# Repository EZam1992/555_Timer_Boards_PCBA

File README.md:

# 555 Timer Board

## Overview

The 555 Timer Board is a beginner-friendly electronics project designed to introduce the author to the process of designing and manufacturing printed circuit boards (PCBs). Using the versatile 555 timer IC, this board provides practical experience with electronic circuit design and real-world prototyping.

---

*Created by Erick Stanley Zamora*  
[erickstanleyzamora.com](https://www.erickstanleyzamora.com/projects/555-timer-board)

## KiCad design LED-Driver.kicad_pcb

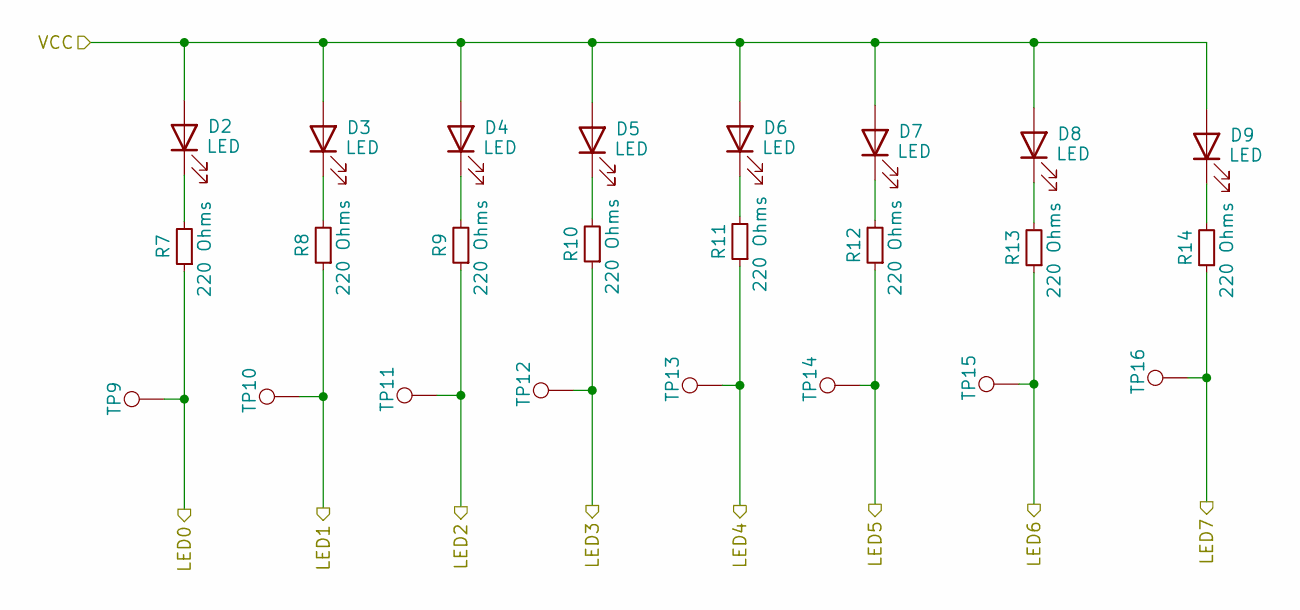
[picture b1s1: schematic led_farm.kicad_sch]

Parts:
D2, D3, D4, D5, D6, D7, D8, D9: LED; LED_D5.0mm
R7, R8, R9, R10, R11, R12, R13, R14: 220 Ohms; R_Axial_DIN0309_L9.0mm_D3.2mm_P12.70mm_Horizontal
TP9, TP10, TP11, TP12, TP13, TP14, TP15, TP16: TestPoint; TestPoint_Loop_D2.50mm_Drill1.0mm_LowProfile

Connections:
/Clock Generation/VCC: D2.2 (A), D3.2 (A), D4.2 (A), D5.2 (A), D6.2 (A), D7.2 (A), D8.2 (A), D9.2 (A); also elsewhere on the board
/Decoder/LED0: R7.1, TP9.1; also elsewhere on the board
/Decoder/LED1: R8.1, TP10.1; also elsewhere on the board
/Decoder/LED2: R9.1, TP11.1; also elsewhere on the board
/Decoder/LED3: R10.1, TP12.1; also elsewhere on the board
/Decoder/LED4: R11.1, TP13.1; also elsewhere on the board
/Decoder/LED5: R12.1, TP14.1; also elsewhere on the board
/Decoder/LED6: R13.1, TP15.1; also elsewhere on the board
/Decoder/LED7: R14.1, TP16.1; also elsewhere on the board
unnamed: D2.1 (K), R7.2
unnamed: D3.1 (K), R8.2
unnamed: D4.1 (K), R9.2
unnamed: D5.1 (K), R10.2
unnamed: D6.1 (K), R11.2
unnamed: D7.1 (K), R12.2
unnamed: D8.1 (K), R13.2
unnamed: D9.1 (K), R14.2

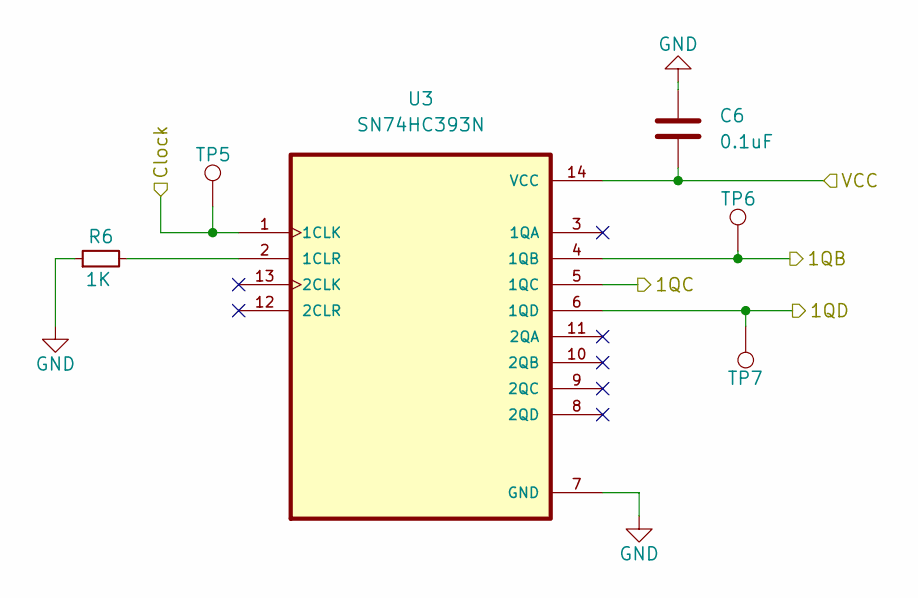
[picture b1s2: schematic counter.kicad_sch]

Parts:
C6: 0.1uF; C_Disc_D6.0mm_W2.5mm_P5.00mm
R6: 1K; R_Axial_DIN0309_L9.0mm_D3.2mm_P12.70mm_Horizontal
TP5, TP6, TP7: TestPoint; TestPoint_Loop_D2.50mm_Drill1.0mm_LowProfile
U3: SN74HC393N

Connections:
/Clock: TP5.1, U3.1 (1CLK); also elsewhere on the board
/Clock Generation/VCC: C6.1, U3.14 (VCC); also elsewhere on the board
/Counter/1QB: TP6.1, U3.4 (1QB); also elsewhere on the board
/Counter/1QC: U3.5 (1QC); also elsewhere on the board
/Counter/1QD: TP7.1, U3.6 (1QD); also elsewhere on the board
GND: C6.2, R6.1, U3.7 (GND); also elsewhere on the board
unnamed: R6.2, U3.2 (1CLR)

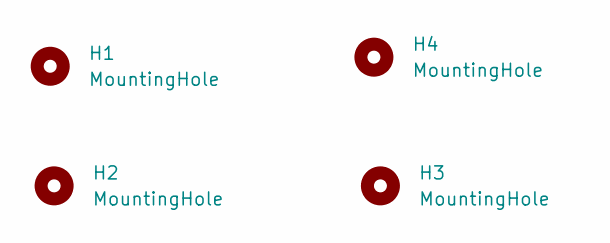
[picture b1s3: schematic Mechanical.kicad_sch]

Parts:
H1, H2, H3, H4: MountingHole; MountingHole_4.3mm_M4_Pad_Via

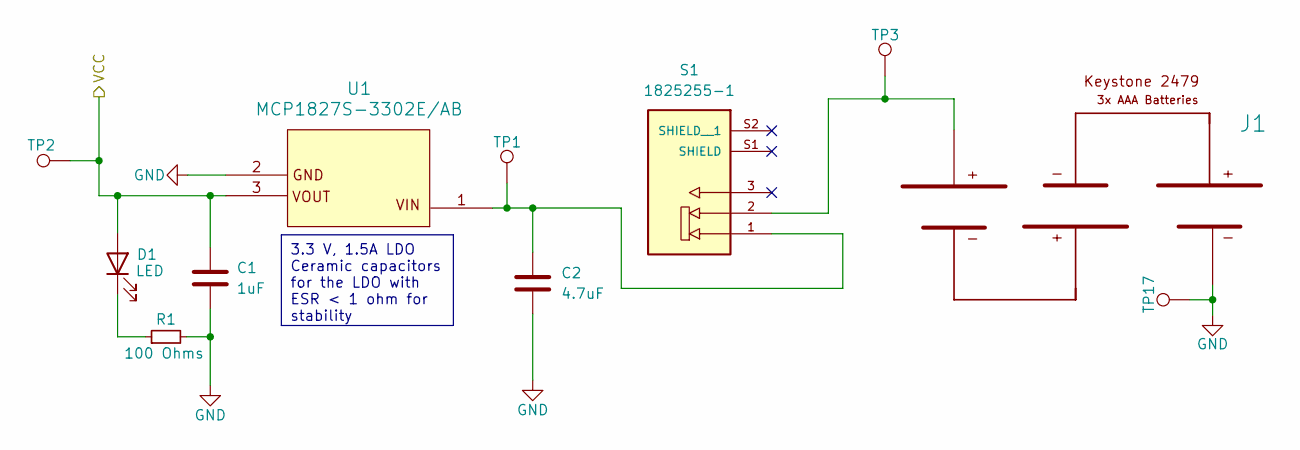
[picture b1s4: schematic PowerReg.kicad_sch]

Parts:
C1: 1uF; C_Disc_D6.0mm_W2.5mm_P5.00mm
C2: 4.7uF; C_Disc_D6.0mm_W2.5mm_P5.00mm
D1: LED; LED_D5.0mm
J1: Keystone_2479
R1: 100 Ohms; R_Axial_DIN0309_L9.0mm_D3.2mm_P12.70mm_Horizontal
S1: 1825255-1; SW_1825255-1
TP1, TP3: TestPoint; TestPoint_Pad_2.0x2.0mm
TP2, TP17: TestPoint; TestPoint_Loop_D2.50mm_Drill1.0mm_LowProfile
U1: MCP1827S-3302E/AB; MCP1827S-3302E

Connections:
/Clock Generation/VCC: C1.1, D1.2 (A), TP2.1, U1.3; also elsewhere on the board
GND: C1.2, C2.2, J1.2, R1.2, TP17.1, U1.2; also elsewhere on the board
unnamed: C2.1, S1.1, TP1.1, U1.1
unnamed: D1.1 (K), R1.1
unnamed: J1.1, S1.2, TP3.1

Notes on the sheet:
3.3 V, 1.5A LDO Ceramic capacitors for the LDO with ESR < 1 ohm for stability

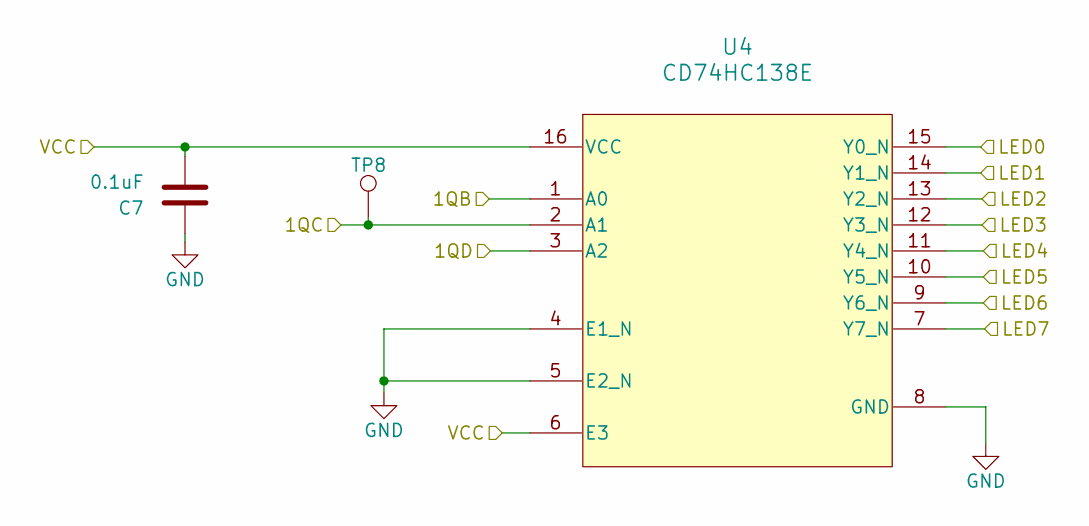
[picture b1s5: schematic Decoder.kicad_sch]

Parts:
C7: 0.1uF; C_Disc_D6.0mm_W2.5mm_P5.00mm
TP8: TestPoint; TestPoint_Loop_D2.50mm_Drill1.0mm_LowProfile
U4: CD74HC138E

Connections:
/Clock Generation/VCC: C7.1, U4.6 (E3), U4.16 (VCC); also elsewhere on the board
/Counter/1QB: U4.1 (A0); also elsewhere on the board
/Counter/1QC: TP8.1, U4.2 (A1); also elsewhere on the board
/Counter/1QD: U4.3 (A2); also elsewhere on the board
/Decoder/LED0: U4.15 (Y0_N); also elsewhere on the board
/Decoder/LED1: U4.14 (Y1_N); also elsewhere on the board
/Decoder/LED2: U4.13 (Y2_N); also elsewhere on the board
/Decoder/LED3: U4.12 (Y3_N); also elsewhere on the board
/Decoder/LED4: U4.11 (Y4_N); also elsewhere on the board
/Decoder/LED5: U4.10 (Y5_N); also elsewhere on the board
/Decoder/LED6: U4.9 (Y6_N); also elsewhere on the board
/Decoder/LED7: U4.7 (Y7_N); also elsewhere on the board
GND: C7.2, U4.4 (E1_N), U4.5 (E2_N), U4.8 (GND); also elsewhere on the board

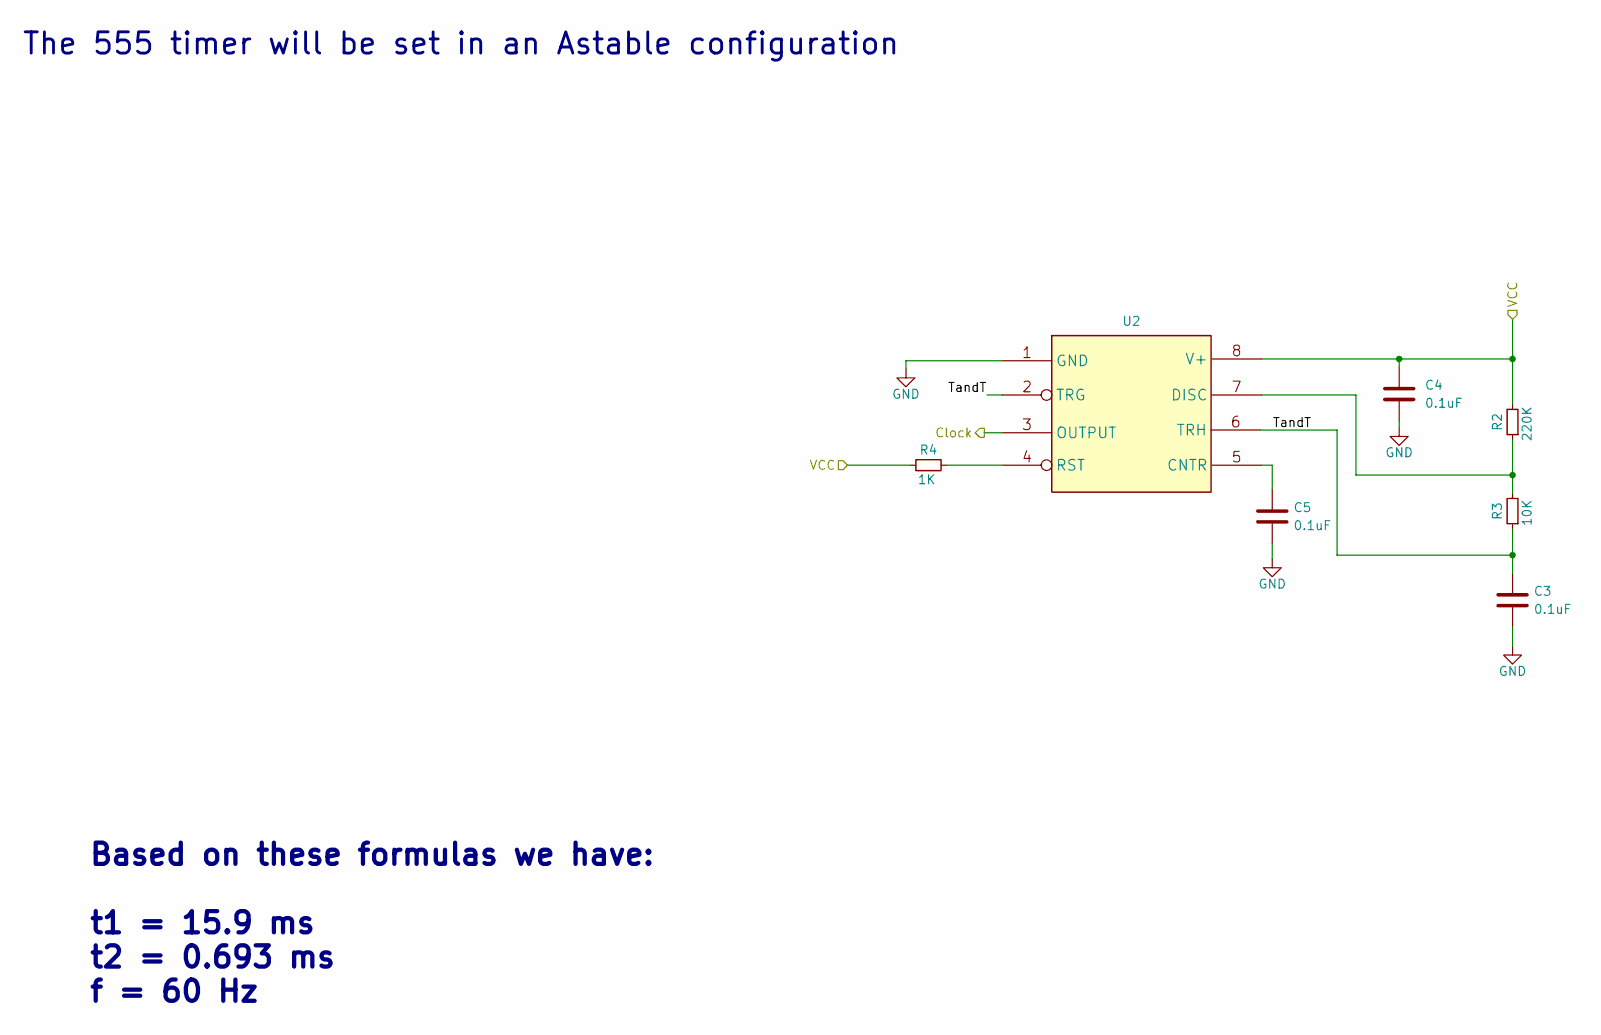
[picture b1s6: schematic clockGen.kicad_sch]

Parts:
C3, C4, C5: 0.1uF; C_Disc_D6.0mm_W2.5mm_P5.00mm
R2: 220K; R_Axial_DIN0309_L9.0mm_D3.2mm_P12.70mm_Horizontal
R3: 10K; R_Axial_DIN0309_L9.0mm_D3.2mm_P12.70mm_Horizontal
R4: 1K; R_Axial_DIN0309_L9.0mm_D3.2mm_P12.70mm_Horizontal
U2: DIP-8_W10.16mm

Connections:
/Clock: U2.3 (OUTPUT); also elsewhere on the board
/Clock Generation/TandT: C3.1, R3.1, U2.2 (TRG), U2.6 (TRH)
/Clock Generation/VCC: C4.1, R2.2, R4.1, U2.8 (V+); also elsewhere on the board
GND: C3.2, C4.2, C5.2, U2.1 (GND); also elsewhere on the board
unnamed: C5.1, U2.5 (CNTR)
unnamed: R2.1, R3.2, U2.7 (DISC)
unnamed: R4.2, U2.4 (RST)

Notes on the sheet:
The 555 timer will be set in an Astable configuration
Based on these formulas we have: t1 = 15.9 ms t2 = 0.693 ms f = 60 Hz

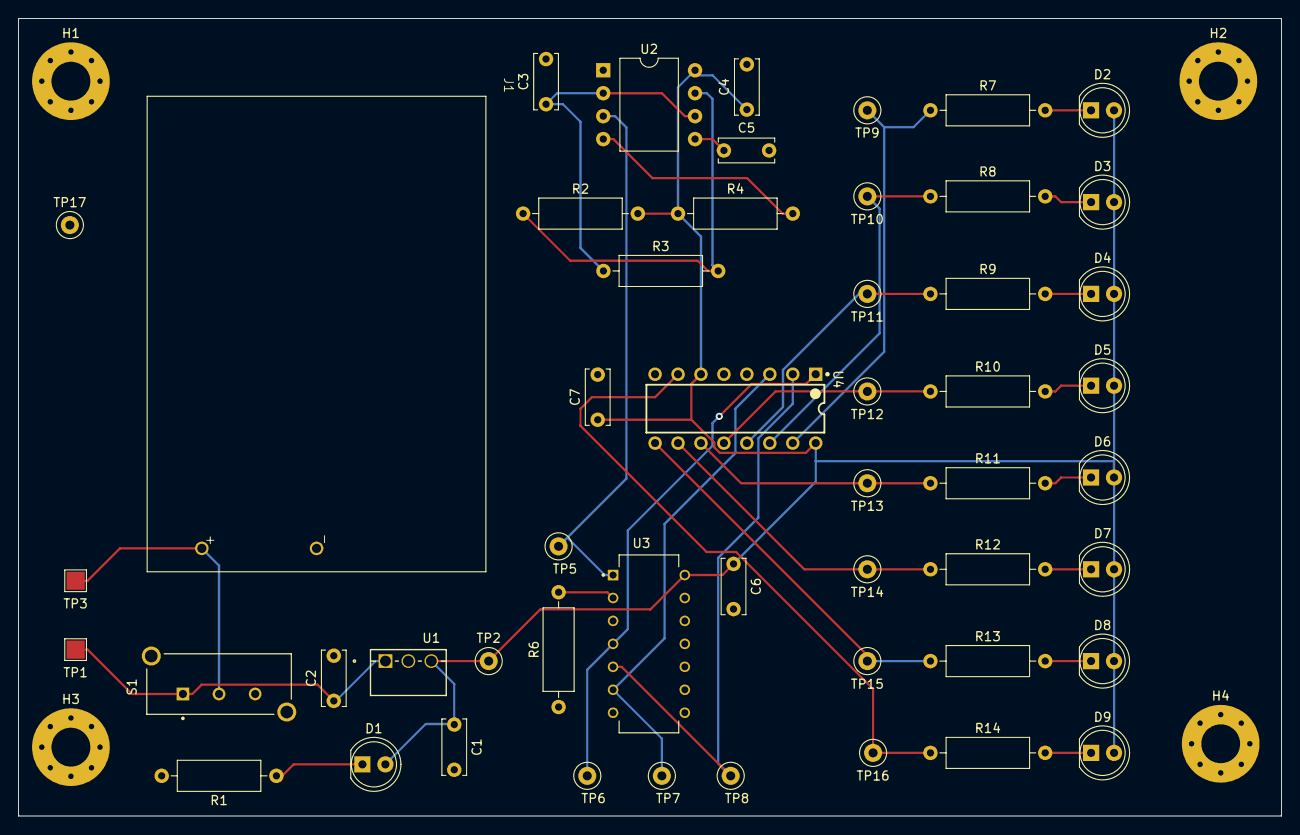
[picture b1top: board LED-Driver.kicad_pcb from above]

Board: 2 copper layers, 139.8 x 88.3 mm, 55 parts (0 on the bottom side), 30 nets.

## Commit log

2025-04-06 moving the PCBA files to Github
